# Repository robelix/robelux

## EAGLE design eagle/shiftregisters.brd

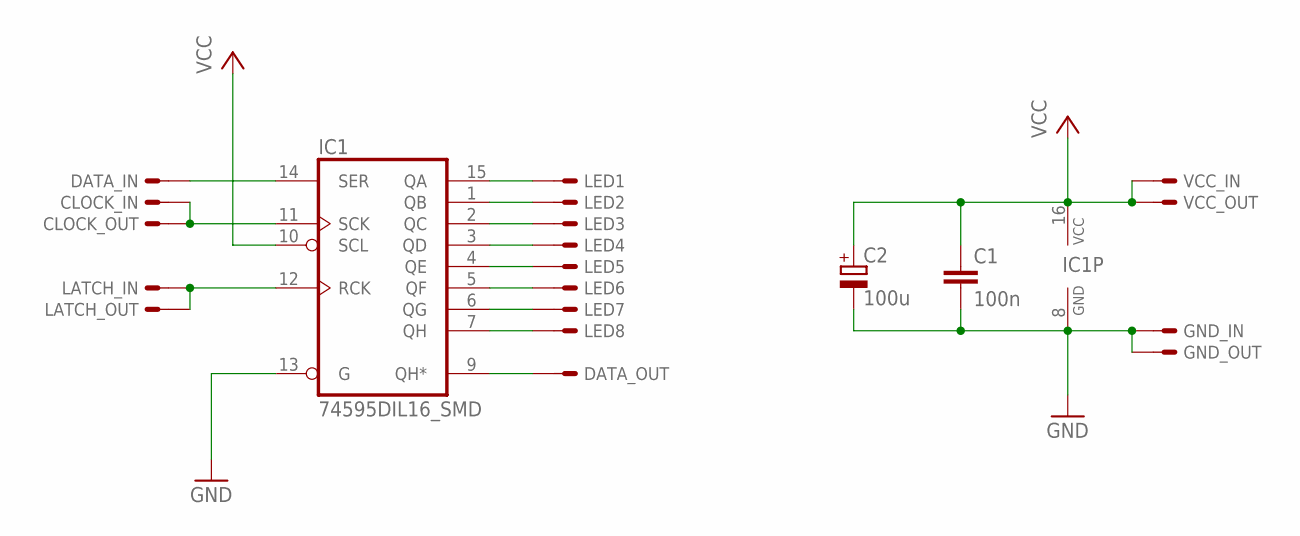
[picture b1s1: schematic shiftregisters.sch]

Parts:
C1: 100n; C0805K
C2: 100u; E2,5-5-L-12SMD
CLOCK_IN: PINS-1-1SMD; SMD
CLOCK_OUT: PINS-1-1SMD; SMD
DATA_IN: PINS-1-1SMD; SMD
DATA_OUT: PINS-1-1SMD; SMD
GND_IN: PINS-1-1SMD; SMD
GND_OUT: PINS-1-1SMD; SMD
IC1: 74595DIL16_SMD; DIL16_SMD
LATCH_IN: PINS-1-1SMD; SMD
LATCH_OUT: PINS-1-1SMD; SMD
LED1, LED2, LED3, LED4, LED5, LED6, LED7, LED8: PINS-1-1SMD; SMD
VCC_IN: PINS-1-1SMD; SMD
VCC_OUT: PINS-1-1SMD; SMD

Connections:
GND: C1.2, C2.-, GND_IN.1, GND_OUT.1, IC1.8 (GND), IC1.13 (G)
unnamed: IC1.15 (QA), LED1.1
unnamed: IC1.1 (QB), LED2.1
unnamed: IC1.2 (QC), LED3.1
unnamed: IC1.3 (QD), LED4.1
unnamed: IC1.4 (QE), LED5.1
unnamed: IC1.5 (QF), LED6.1
unnamed: IC1.6 (QG), LED7.1
unnamed: IC1.7 (QH), LED8.1
unnamed: DATA_IN.1, IC1.14 (SER)
unnamed: DATA_OUT.1, IC1.9 (QH*)
unnamed: CLOCK_IN.1, CLOCK_OUT.1, IC1.11 (SCK)
unnamed: IC1.12 (RCK), LATCH_IN.1, LATCH_OUT.1
VCC: C1.1, C2.+, IC1.10 (SCL), IC1.16 (VCC), VCC_IN.1, VCC_OUT.1

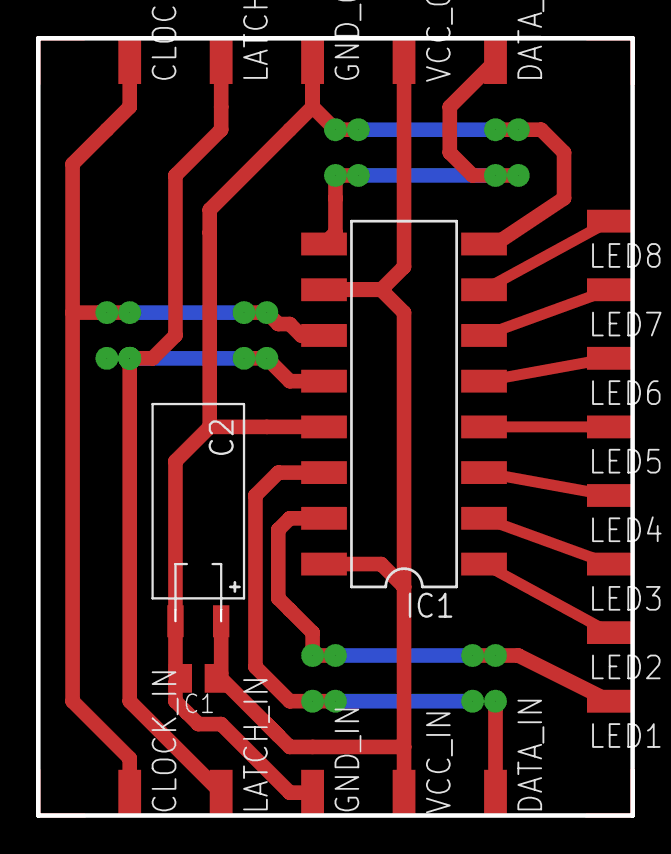
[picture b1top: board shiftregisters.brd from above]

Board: 2 copper layers, 33.0 x 43.2 mm, 21 parts (0 on the bottom side), 14 nets.
